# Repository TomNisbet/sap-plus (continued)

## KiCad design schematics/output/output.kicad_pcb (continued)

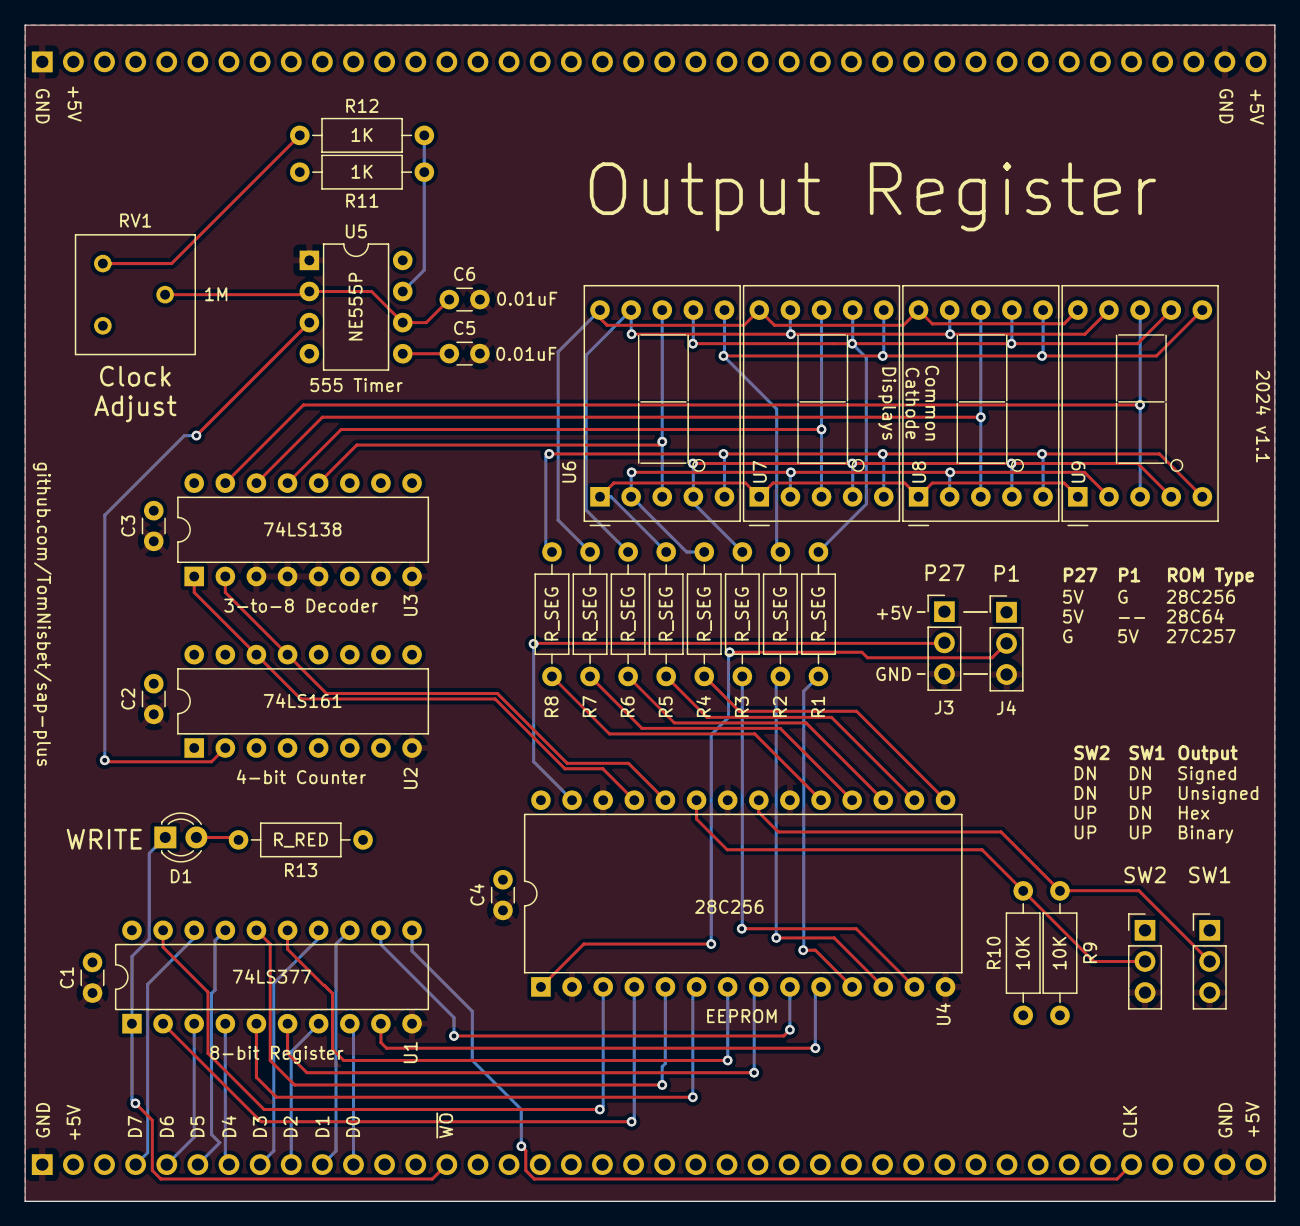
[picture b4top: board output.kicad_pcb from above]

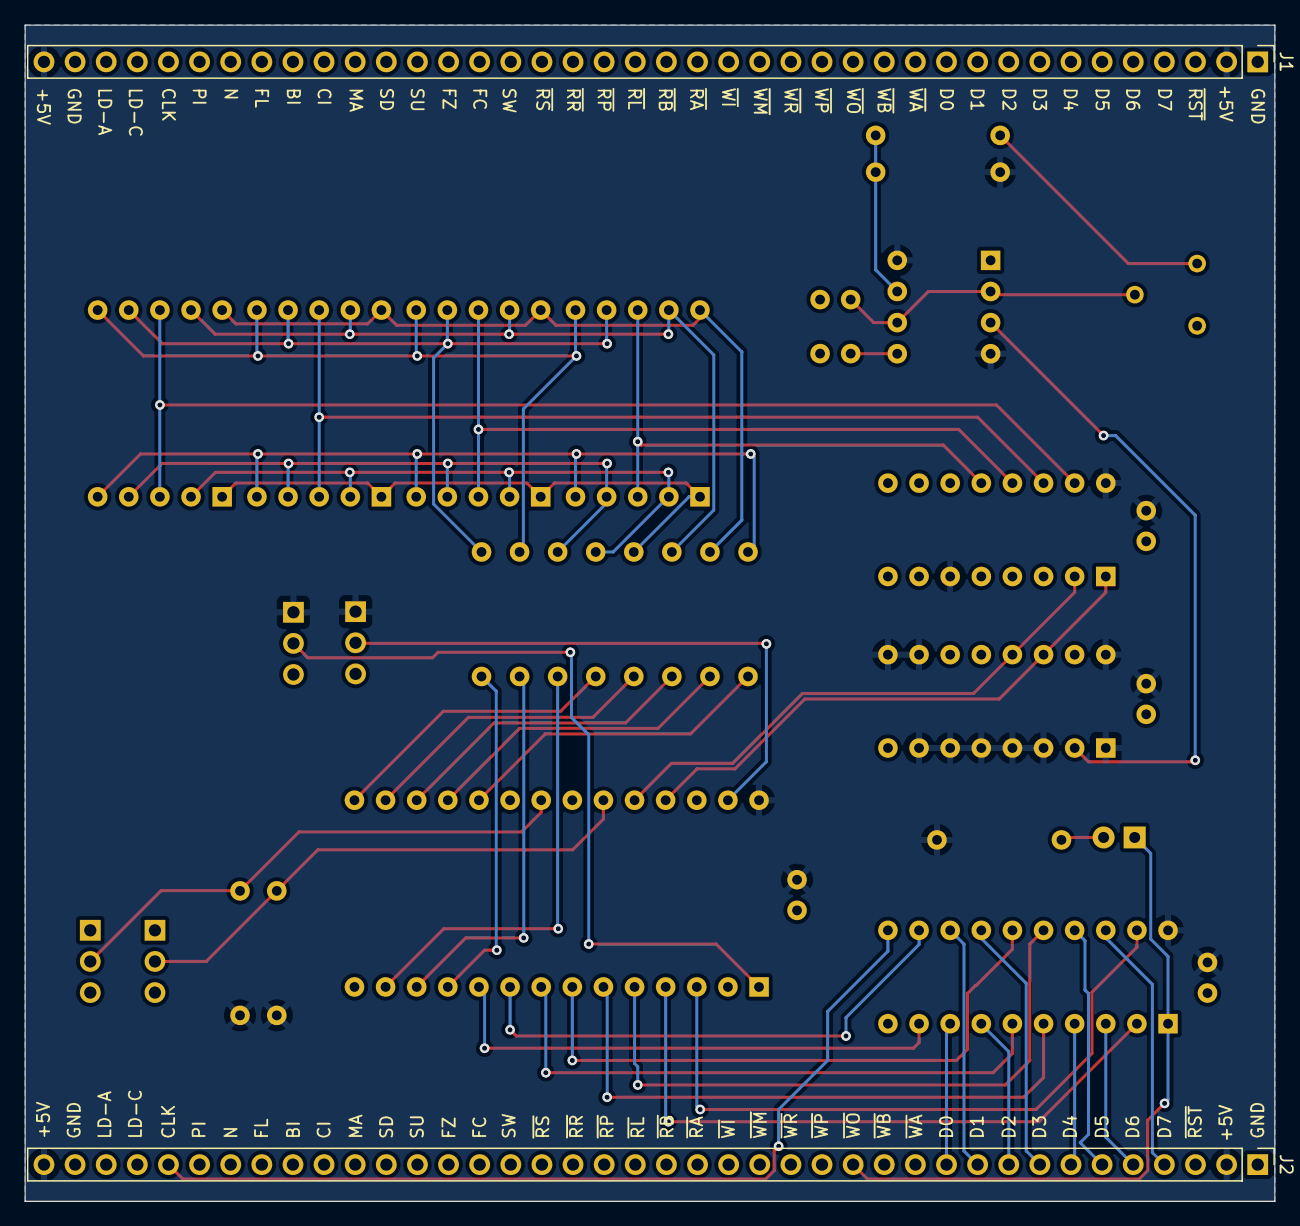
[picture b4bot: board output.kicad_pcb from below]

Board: 2 copper layers, 102.0 x 96.0 mm, 36 parts (2 on the bottom side), 52 nets.

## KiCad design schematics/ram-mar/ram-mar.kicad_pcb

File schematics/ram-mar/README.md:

# RAM and Memory Address Register Module schematics

created with KiCad 8.0

## Changelog

### 1.1

* Update resistor network values to match LEDs

### 1.0

* Initial version

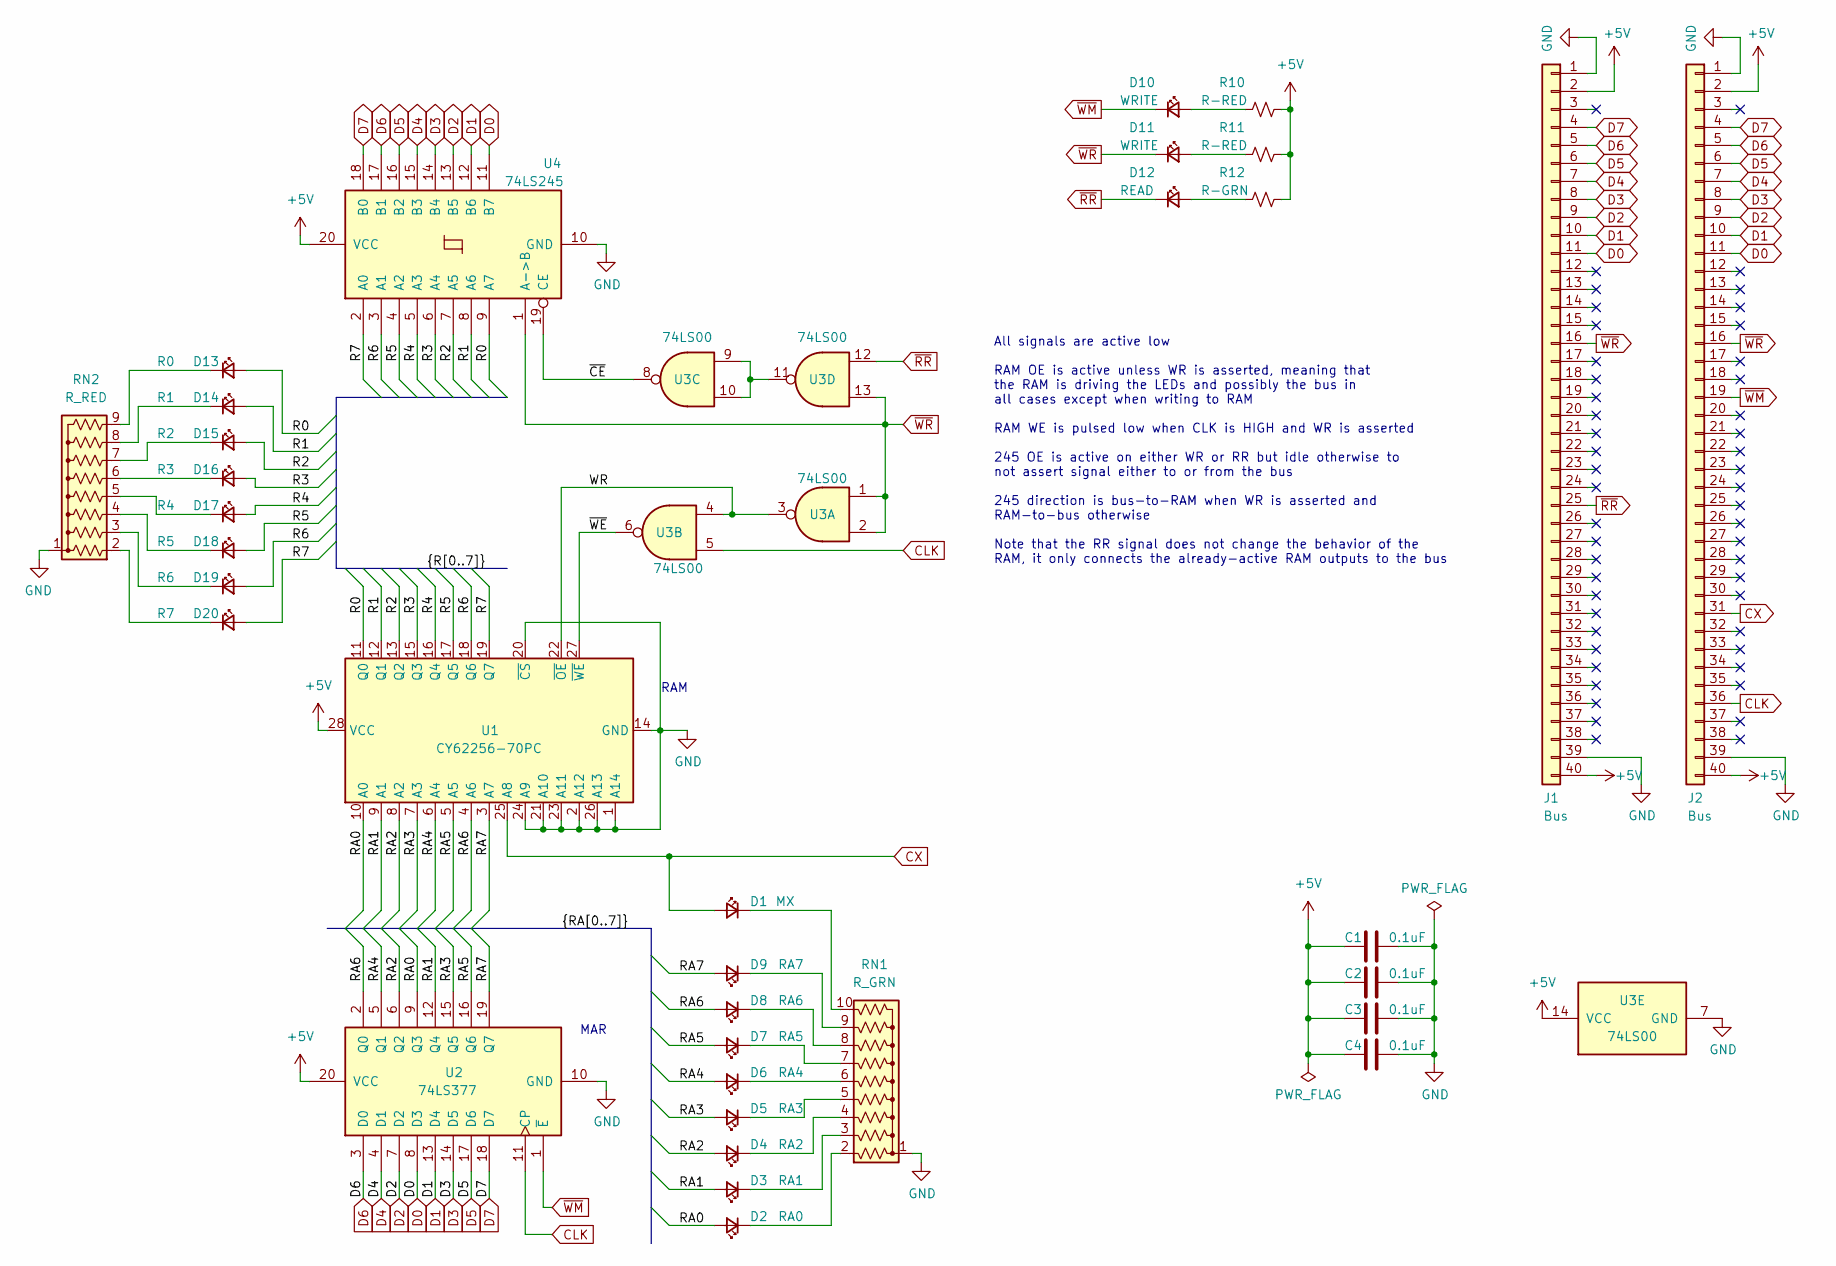
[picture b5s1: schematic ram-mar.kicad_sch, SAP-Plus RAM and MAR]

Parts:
C1, C2, C3, C4: 0.1uF; C_Disc_D3.0mm_W2.0mm_P2.50mm
D1: MX; LED_D3.0mm
D2: RA0; LED_D3.0mm
D3: RA1; LED_D3.0mm
D4: RA2; LED_D3.0mm
D5: RA3; LED_D3.0mm
D6: RA4; LED_D3.0mm
D7: RA5; LED_D3.0mm
D8: RA6; LED_D3.0mm
D9: RA7; LED_D3.0mm
D10, D11: WRITE; LED_D3.0mm
D12: READ; LED_D3.0mm
D13: R0; LED_D3.0mm
D14: R1; LED_D3.0mm
D15: R2; LED_D3.0mm
D16: R3; LED_D3.0mm
D17: R4; LED_D3.0mm
D18: R5; LED_D3.0mm
D19: R6; LED_D3.0mm
D20: R7; LED_D3.0mm
J1, J2: Bus; PinHeader_1x40_P2.54mm_Vertical
R10, R11: R-RED; R_Axial_DIN0207_L6.3mm_D2.5mm_P10.16mm_Horizontal
R12: R-GRN; R_Axial_DIN0207_L6.3mm_D2.5mm_P10.16mm_Horizontal
RN1: R_GRN; R_Array_SIP10
RN2: R_RED; R_Array_SIP9
U1: CY62256-70PC; DIP-28_W15.24mm_Socket
U2: 74LS377; DIP-20_W7.62mm
U3: 74LS00; DIP-14_W7.62mm
U4: 74LS245; DIP-20_W7.62mm

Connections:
+5V: C1.2, C2.2, C3.2, C4.2, J1.2, J1.40, J2.2, J2.40, R10.1, R11.1, R12.1, U1.28 (VCC), U2.20 (VCC), U3.14 (VCC), U4.20 (VCC)
/R0: D13.2 (A), U1.11 (Q0), U4.9 (A7)
/R1: D14.2 (A), U1.12 (Q1), U4.8 (A6)
/R2: D15.2 (A), U1.13 (Q2), U4.7 (A5)
/R3: D16.2 (A), U1.15 (Q3), U4.6 (A4)
/R4: D17.2 (A), U1.16 (Q4), U4.5 (A3)
/R5: D18.2 (A), U1.17 (Q5), U4.4 (A2)
/R6: D19.2 (A), U1.18 (Q6), U4.3 (A1)
/R7: D20.2 (A), U1.19 (Q7), U4.2 (A0)
/RA0: D2.2 (A), U1.10 (A0), U2.9 (Q3)
/RA1: D3.2 (A), U1.9 (A1), U2.12 (Q4)
/RA2: D4.2 (A), U1.8 (A2), U2.6 (Q2)
/RA3: D5.2 (A), U1.7 (A3), U2.15 (Q5)
/RA4: D6.2 (A), U1.6 (A4), U2.5 (Q1)
/RA5: D7.2 (A), U1.5 (A5), U2.16 (Q6)
/RA6: D8.2 (A), U1.4 (A6), U2.2 (Q0)
/RA7: D9.2 (A), U1.3 (A7), U2.19 (Q7)
/WR: U1.22 (~OE), U3.3, U3.4
/~CE: U3.8, U4.19 (CE)
/~WE: U1.27 (~WE), U3.6
CLK: J2.36, U2.11 (CP), U3.5
CX: D1.2 (A), J2.31, U1.25 (A8)
D0: J1.11, J2.11, U2.8 (D3), U4.11 (B7)
D1: J1.10, J2.10, U2.13 (D4), U4.12 (B6)
D2: J1.9, J2.9, U2.7 (D2), U4.13 (B5)
D3: J1.8, J2.8, U2.14 (D5), U4.14 (B4)
D4: J1.7, J2.7, U2.4 (D1), U4.15 (B3)
D5: J1.6, J2.6, U2.17 (D6), U4.16 (B2)
D6: J1.5, J2.5, U2.3 (D0), U4.17 (B1)
D7: J1.4, J2.4, U2.18 (D7), U4.18 (B0)
GND: C1.1, C2.1, C3.1, C4.1, J1.1, J1.39, J2.1, J2.39, RN1.1 (common), RN2.1 (common), U1.1 (A14), U1.2 (A12), U1.14 (GND), U1.20 (~CS), U1.21 (A10), U1.23 (A11), U1.24 (A9), U1.26 (A13), U2.10 (GND), U3.7 (GND), U4.10 (GND)
unnamed: D1.1 (K), RN1.10 (R9)
unnamed: D2.1 (K), RN1.2 (R1)
unnamed: D3.1 (K), RN1.3 (R2)
unnamed: D4.1 (K), RN1.4 (R3)
unnamed: D5.1 (K), RN1.5 (R4)
unnamed: D6.1 (K), RN1.6 (R5)
unnamed: D7.1 (K), RN1.7 (R6)
unnamed: D8.1 (K), RN1.8 (R7)
unnamed: D9.1 (K), RN1.9 (R8)
unnamed: D10.2 (A), R10.2
unnamed: D11.2 (A), R11.2
unnamed: D12.2 (A), R12.2
unnamed: D13.1 (K), RN2.9 (R8)
unnamed: D14.1 (K), RN2.8 (R7)
unnamed: D15.1 (K), RN2.7 (R6)
unnamed: D16.1 (K), RN2.6 (R5)
unnamed: D17.1 (K), RN2.5 (R4)
unnamed: D18.1 (K), RN2.4 (R3)
unnamed: D19.1 (K), RN2.3 (R2)
unnamed: D20.1 (K), RN2.2 (R1)
unnamed: U3.9, U3.10, U3.11
~RR: D12.1 (K), J1.25, U3.12
~WM: D10.1 (K), J2.19, U2.1 (~E)
~WR: D11.1 (K), J1.16, J2.16, U3.1, U3.2, U3.13, U4.1 (A->B)

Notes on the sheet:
All signals are active low RAM OE is active unless WR is asserted, meaning that the RAM is driving the LEDs and possibly the bus in all cases except when writing to RAM RAM WE is pulsed low when CLK is HIGH and WR is asserted 245 OE is active on either WR or RR but idle otherwise to not assert sign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
MAR
RAM

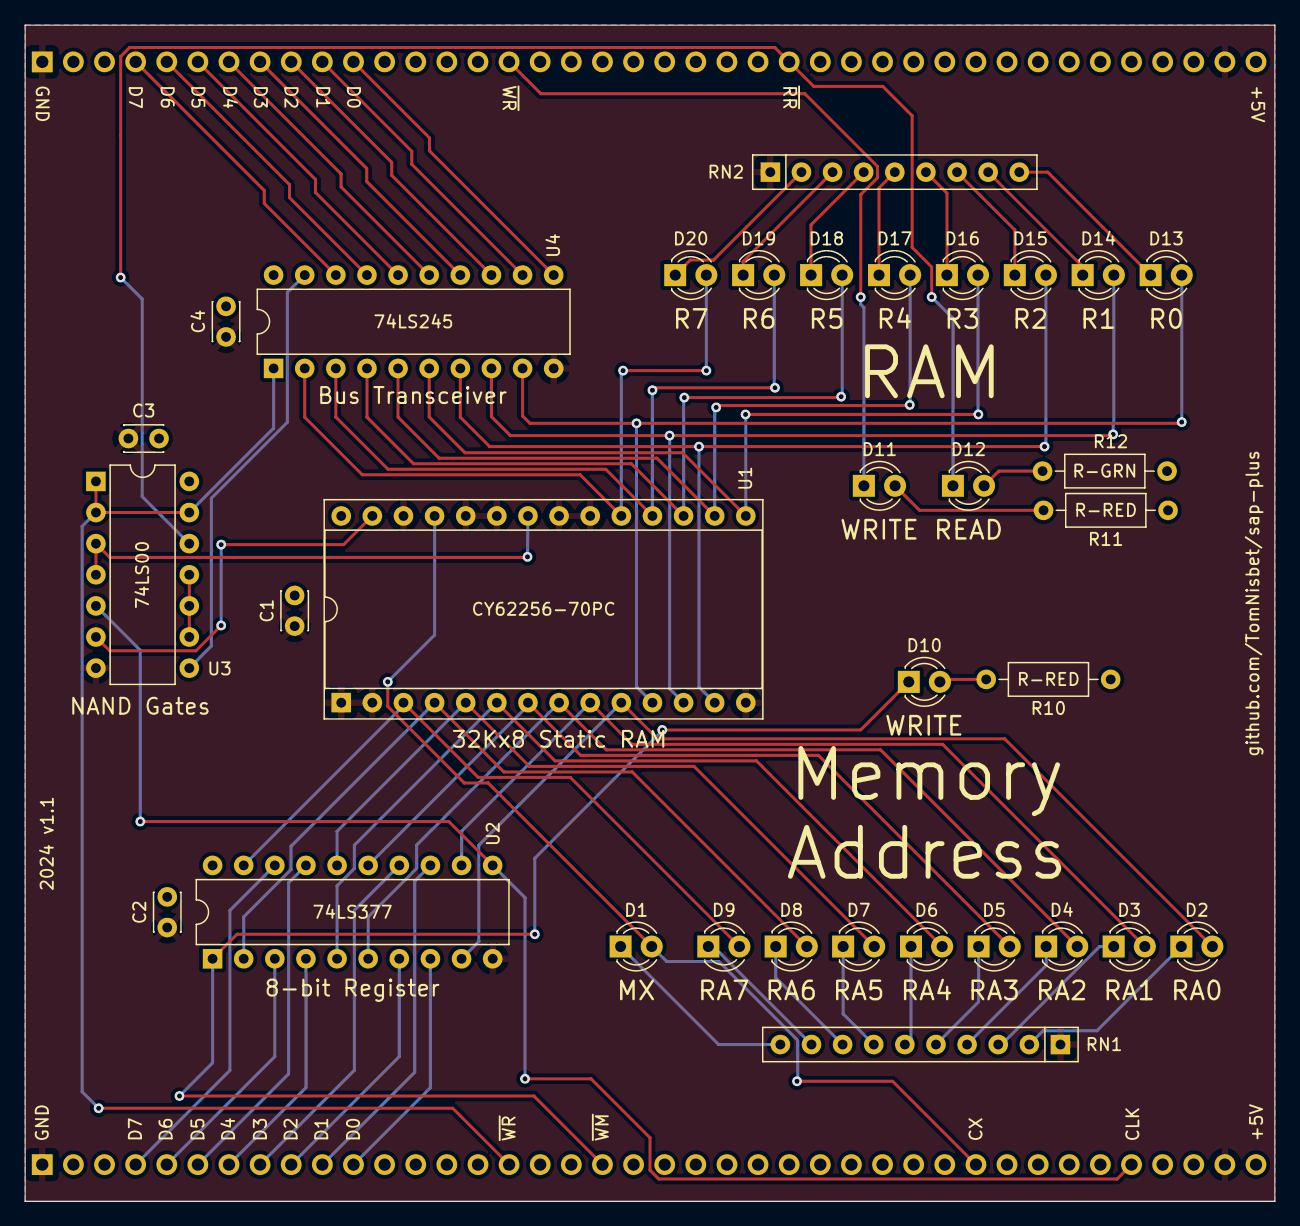
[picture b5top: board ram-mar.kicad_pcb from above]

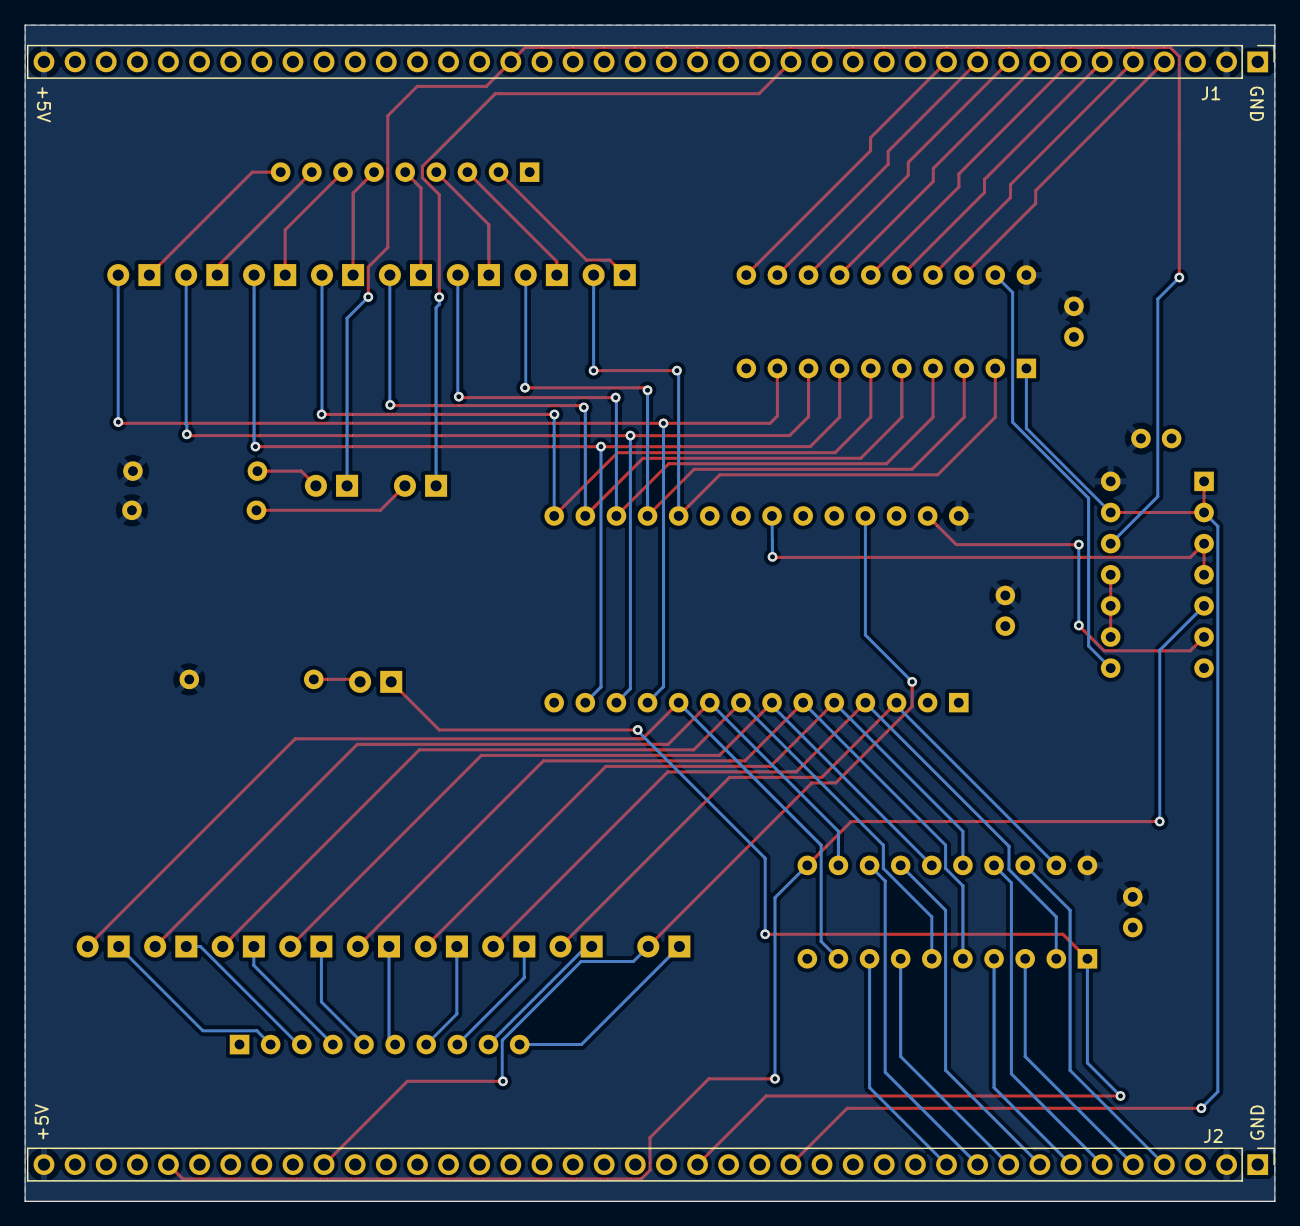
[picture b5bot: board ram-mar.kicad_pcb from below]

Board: 2 copper layers, 102.0 x 96.0 mm, 35 parts (2 on the bottom side), 55 nets.
